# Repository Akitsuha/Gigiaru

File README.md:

<div id="top"></div>

<!-- プロジェクトについて -->

## プロジェクトについて

ポケモン「ギギアル」のペットロボットを作るプロジェクト

## リポジトリ構成
<pre>
    .
├── README.md
├── code
│   ├── data
│   ├── firmware.elf
│   ├── include
│   ├── lib
│   ├── platformio.ini
│   ├── src //主に書いたコード
│   └── test
├── electonics //電子回路コンポーネントの設計
└── hardware //3DCAD設計
</pre>

<p align="right">(<a href="#top">トップへ</a>)</p>

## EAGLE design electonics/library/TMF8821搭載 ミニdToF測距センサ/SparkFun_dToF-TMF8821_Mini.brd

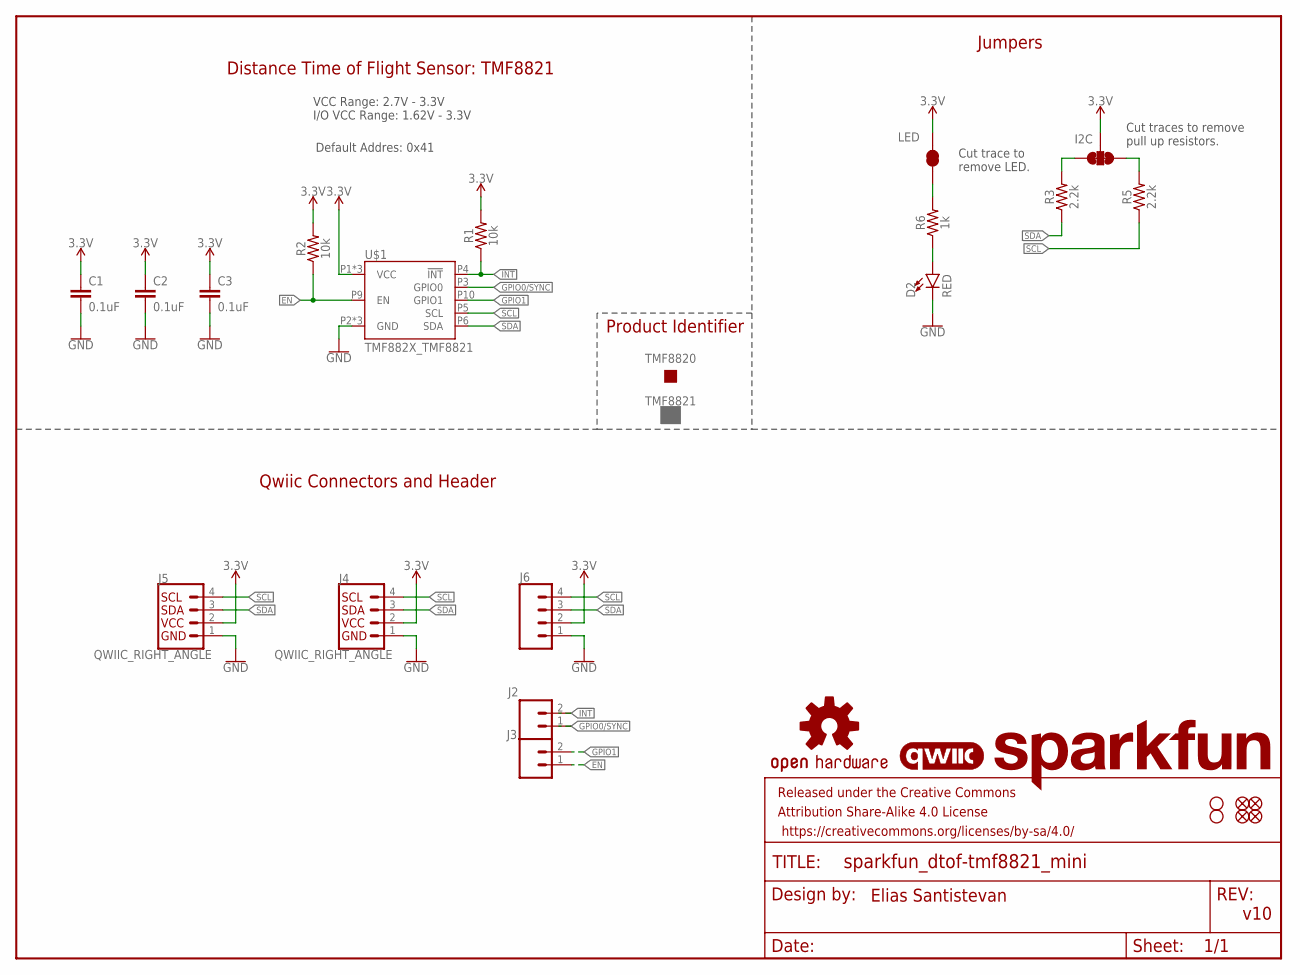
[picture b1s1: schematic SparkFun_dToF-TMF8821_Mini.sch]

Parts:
C1, C2, C3: 0.1uF; 0402-TIGHT
D2: RED; LED-0603
FD5, FD6, FD7, FD8: FIDUCIALUFIDUCIAL; FIDUCIAL-MICRO
FRAME2: FRAME-LETTER; CREATIVE_COMMONS
H7, H8: STAND-OFFTIGHT; STAND-OFF-TIGHT
I2C: I2C_PU; SMT-JUMPER_3_2-NC_TRACE_SILK
J2, J3: CONN_021X02_NO_SILK; 1X02_NO_SILK
J4, J5: QWIIC_RIGHT_ANGLE; JST04_1MM_RA
J6: CONN_041X04_NO_SILK; 1X04_NO_SILK
LED: LED; SMT-JUMPER_2_NC_TRACE_SILK
LOGO1: SFE_LOGO_NAMEBLANK; BLANK
LOGO2: QWIIC_LOGO_4MM; QWIIC_4MM
LOGO3: OSHW-LOGONO_SILK; DUMMY
R1, R2: 10k; 0402-TIGHT
R3, R5: 2.2k; 0402-TIGHT
R6: 1k; 0402-TIGHT
TMF8820: PROD_ID_NO-PASTE_SILK; PRODUCT_IDENT_NO_SILK
TMF8821: PROD_ID_PASTE_SILK; PRODUCT_IDENT_PASTE_SILK
U$1: TMF882X_TMF8821; TMF882X

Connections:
3.3V: C1.1, C2.1, C3.1, I2C.2, J4.2, J5.2, J6.2, LED.2, R1.2, R2.2, U$1.P1 (VCC), U$1.P7 (VCC), U$1.P12 (VCC)
!INT!: J2.2, R1.1, U$1.P4 (!INT!)
EN: J3.1, R2.1, U$1.P9 (EN)
GND: C1.2, C2.2, C3.2, D2.C, J4.1, J5.1, J6.1, U$1.P2 (GND), U$1.P8 (GND), U$1.P11 (GND)
GPIO0/SYNC: J2.1, U$1.P3 (GPIO0)
GPIO1: J3.2, U$1.P10 (GPIO1)
unnamed: D2.A, R6.1
unnamed: LED.1, R6.2
unnamed: I2C.3, R3.2
unnamed: I2C.1, R5.2
SCL: J4.4, J5.4, J6.4, R5.1, U$1.P5 (SCL)
SDA: J4.3, J5.3, J6.3, R3.1, U$1.P6 (SDA)

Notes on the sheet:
v10
Qwiic Connectors and Header
Jumpers
Cut trace to remove LED.
Cut traces to remove pull up resistors.
Elias Santistevan
Distance Time of Flight Sensor: TMF8821
VCC Range: 2.7V - 3.3V I/O VCC Range: 1.62V - 3.3V
Default Addres: 0x41
Product Identifier

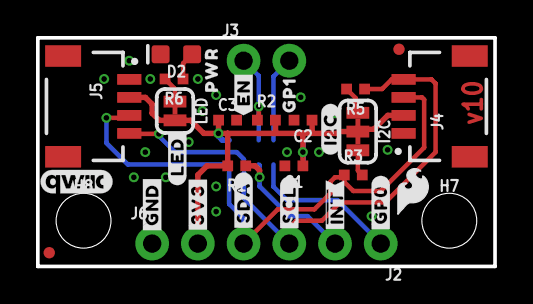
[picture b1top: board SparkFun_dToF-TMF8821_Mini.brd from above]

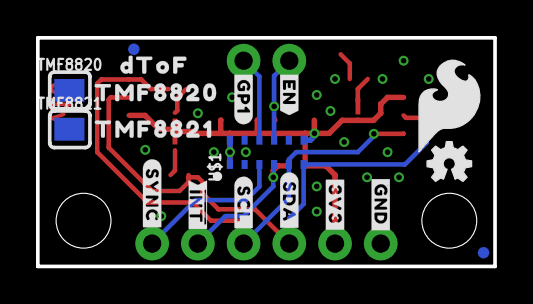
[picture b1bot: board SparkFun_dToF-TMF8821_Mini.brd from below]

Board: 2 copper layers, 25.4 x 12.7 mm, 54 parts (18 on the bottom side), 12 nets.

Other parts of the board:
U$2: #LED#10
U$3: ##INT##9
U$4: ##INT##8
U$5: #SYNC#8
U$6: #GP1#8
U$7: DTOF882188211
U$8: TMF882020
U$9, U$31: #EN#7
U$10, U$37: #3V3#0
U$11: TMF882188210
U$12: GP18
U$13: #GP0#19
U$14: SFE_LOGO_FLAME_.2
U$15: OSHW-LOGO-MINI
U$16, U$38: #GND#4
U$18, U$40: #SDA#6
U$19, U$39: #SCL#5
U$20: #I2C#11
U$35: SFE_LOGO_FLAME_.1
U$43: PWR8821882023

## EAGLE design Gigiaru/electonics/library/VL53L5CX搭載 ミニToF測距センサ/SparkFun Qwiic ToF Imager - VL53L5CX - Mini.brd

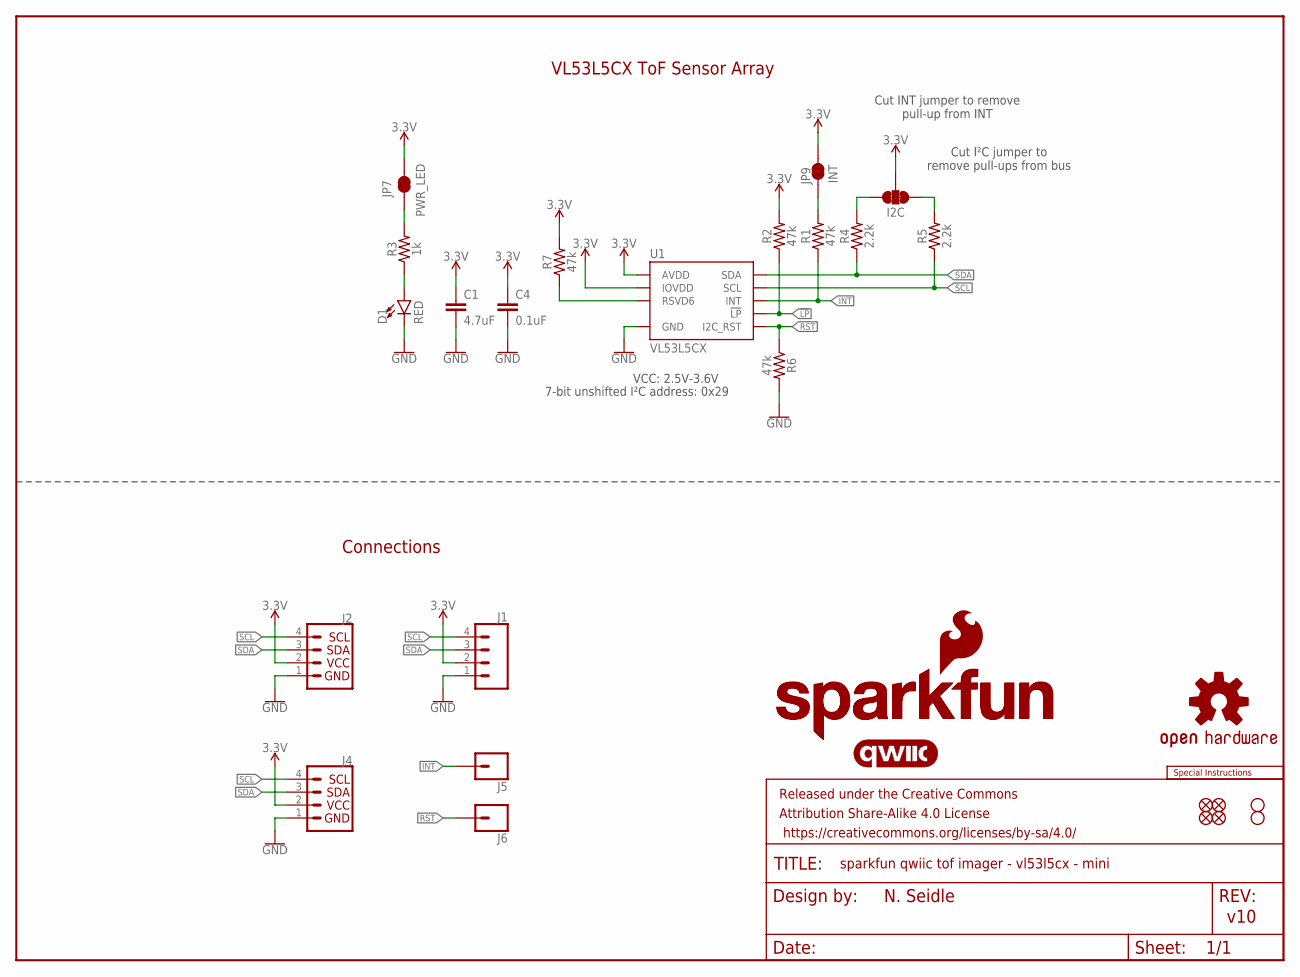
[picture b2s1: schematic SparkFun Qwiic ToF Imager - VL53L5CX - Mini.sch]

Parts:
C1: 4.7uF; 0402-TIGHT
C4: 0.1uF; 0402-TIGHT
D1: RED; LED-0603
FRAME1: FRAME-LETTER; CREATIVE_COMMONS
I2C: JUMPER-SMT_3_2-NC_TRACE_SILK; SMT-JUMPER_3_2-NC_TRACE_SILK
J1: CONN_041X04_NO_SILK; 1X04_NO_SILK
J2, J4: Vertical Qwiic Connector; JST04_1MM_VERT
J5, J6: CONN_01PTH_NO_SILK_YES_STOP; 1X01_NO_SILK
JP1, JP2, JP5, JP6: FIDUCIALUFIDUCIAL; FIDUCIAL-MICRO
JP7: PWR_LED; SMT-JUMPER_2_NC_TRACE_SILK
JP9: INT; SMT-JUMPER_2_NC_TRACE_SILK
JP10, JP11: STAND-OFF
LOGO1: SFE_LOGO_NAME_FLAME8_MM; SFE_LOGO_NAME_FLAME_8MM
LOGO2: OSHW-LOGONO_SILK; DUMMY
LOGO3: QWIIC_LOGO_CONNECTOR; QWIIC_5.5MM
LOGO4: SFE_LOGO_NAME6_MM; SFE_LOGO_NAME_6MM
LOGO5: SPECIAL_INSTRUCTIONS-ORDERING; ORDERING_INSTRUCTIONS
R1, R2, R6, R7: 47k; 0402-TIGHT
R3: 1k; 0402-TIGHT
R4, R5: 2.2k; 0402-TIGHT
U1: VL53L5CX

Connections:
3.3V: C1.1, C4.1, I2C.2, J1.2, J2.2, J4.2, JP7.2, JP9.2, R2.2, R7.2, U1.A4 (IOVDD), U1.B1 (AVDD), U1.B7 (AVDD)
!LP: R2.1, U1.A5 (!LP)
GND: C1.2, C4.2, D1.C, J1.1, J2.1, J4.1, R6.2, U1.A2 (GND), U1.A6 (GND), U1.A7 (GND), U1.B4 (GND), U1.C1 (GND), U1.C6 (GND), U1.C7 (GND)
INT: J5.1, R1.1, U1.A3 (INT)
unnamed: I2C.1, R5.2
unnamed: I2C.3, R4.2
unnamed: D1.A, R3.1
unnamed: JP9.1, R1.2
unnamed: JP7.1, R3.2
unnamed: R7.1, U1.C2 (RSVD6)
RST: J6.1, R6.1, U1.A1 (I2C_RST)
SCL: J1.4, J2.4, J4.4, R5.1, U1.C4 (SCL)
SDA: J1.3, J2.3, J4.3, R4.1, U1.C3 (SDA)

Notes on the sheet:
N. Seidle
v10
7-bit unshifted I²C address: 0x29
Cut I²C jumper to remove pull-ups from bus
Cut INT jumper to remove pull-up from INT
VCC: 2.5V-3.6V
VL53L5CX ToF Sensor Array
Connections

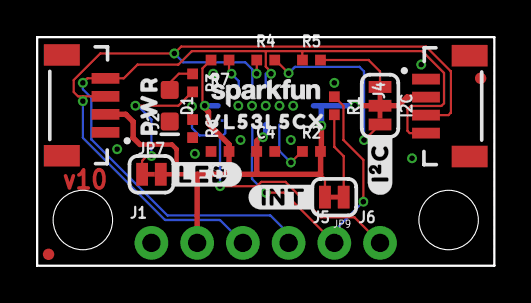
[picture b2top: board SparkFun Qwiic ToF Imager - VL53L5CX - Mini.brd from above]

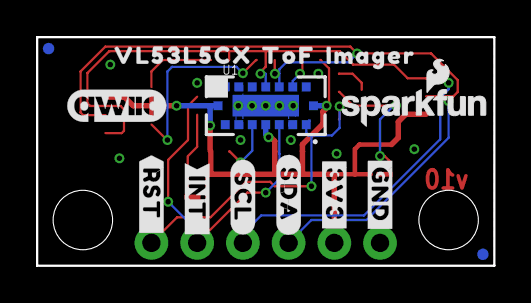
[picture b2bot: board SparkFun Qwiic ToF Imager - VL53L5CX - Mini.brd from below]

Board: 2 copper layers, 25.4 x 12.7 mm, 45 parts (14 on the bottom side), 13 nets.

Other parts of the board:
U$1: VL53L5CX_0
U$2: #LED#0
U$3: #3V3#13
U$4: PWR12
U$5: #INT#0
U$8: #INT_#0
U$9: #RST_#1
U$16: #I�C#0
U$19: VL53L5CX0
U$20: TOF1
U$22: IMAGER2
U$24: #SCL#1
U$25: #SDA#0
U$30: #GND#62130

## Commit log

2023-03-20 ひさしぶり
2023-03-21 フォルダ整理
2023-04-21 いろいろ
2023-04-24 一旦動くやつ
2023-04-24 記憶を構造体化
2023-04-24 モーションのクラス化、記録
2023-12-19 不要ファイル削除
2023-12-19 フォルダ展開
2023-12-19 重複ファイルの削除
    icloud連携のせいで重複してしまったファイルを削除。
    連携外のフォルダに引っ越しした
2023-12-19 ファイル整理
    重複ファイル、旧バージョンファイル消去
    STLファイルのリネーム

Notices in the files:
parts and their libraries:
SparkFun-Resistors: Licensing: Creative Commons ShareAlike 4.0 International - https://creativecommons.org/licenses/by-sa/4.0
SparkFun-Aesthetics: Released under the Creative Commons Attribution Share-Alike 4.0 License
SparkFun-Aesthetics: https://creativecommons.org/licenses/by-sa/4.0
